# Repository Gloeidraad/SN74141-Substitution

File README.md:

The SN74141 is an obsolete device intended for diving nixie tubes. However, even today, enthusiasts still love nixie tubes. Sometimes by building digital clocks with nixies, but also keeping vintage equivalent alive. In the old days, very often the nixie tubes are driven by the good old SN74141 device. These devices (or the soviet K155ID1) can still be found on the internet, but stocks are dwindling. I tried to make a replacement circuit which should fit on the location of the original DIL-16 footprint of the SN74141. 

Because of the limited size of the DIL-16 socket, I had to use the smallest devices possible, so if you want to use the design, be sure you are capable to solder TSSOP devices.

The design is not implement on a real PCBA yet, so please test it yourself before placing it in al valuable instrument.

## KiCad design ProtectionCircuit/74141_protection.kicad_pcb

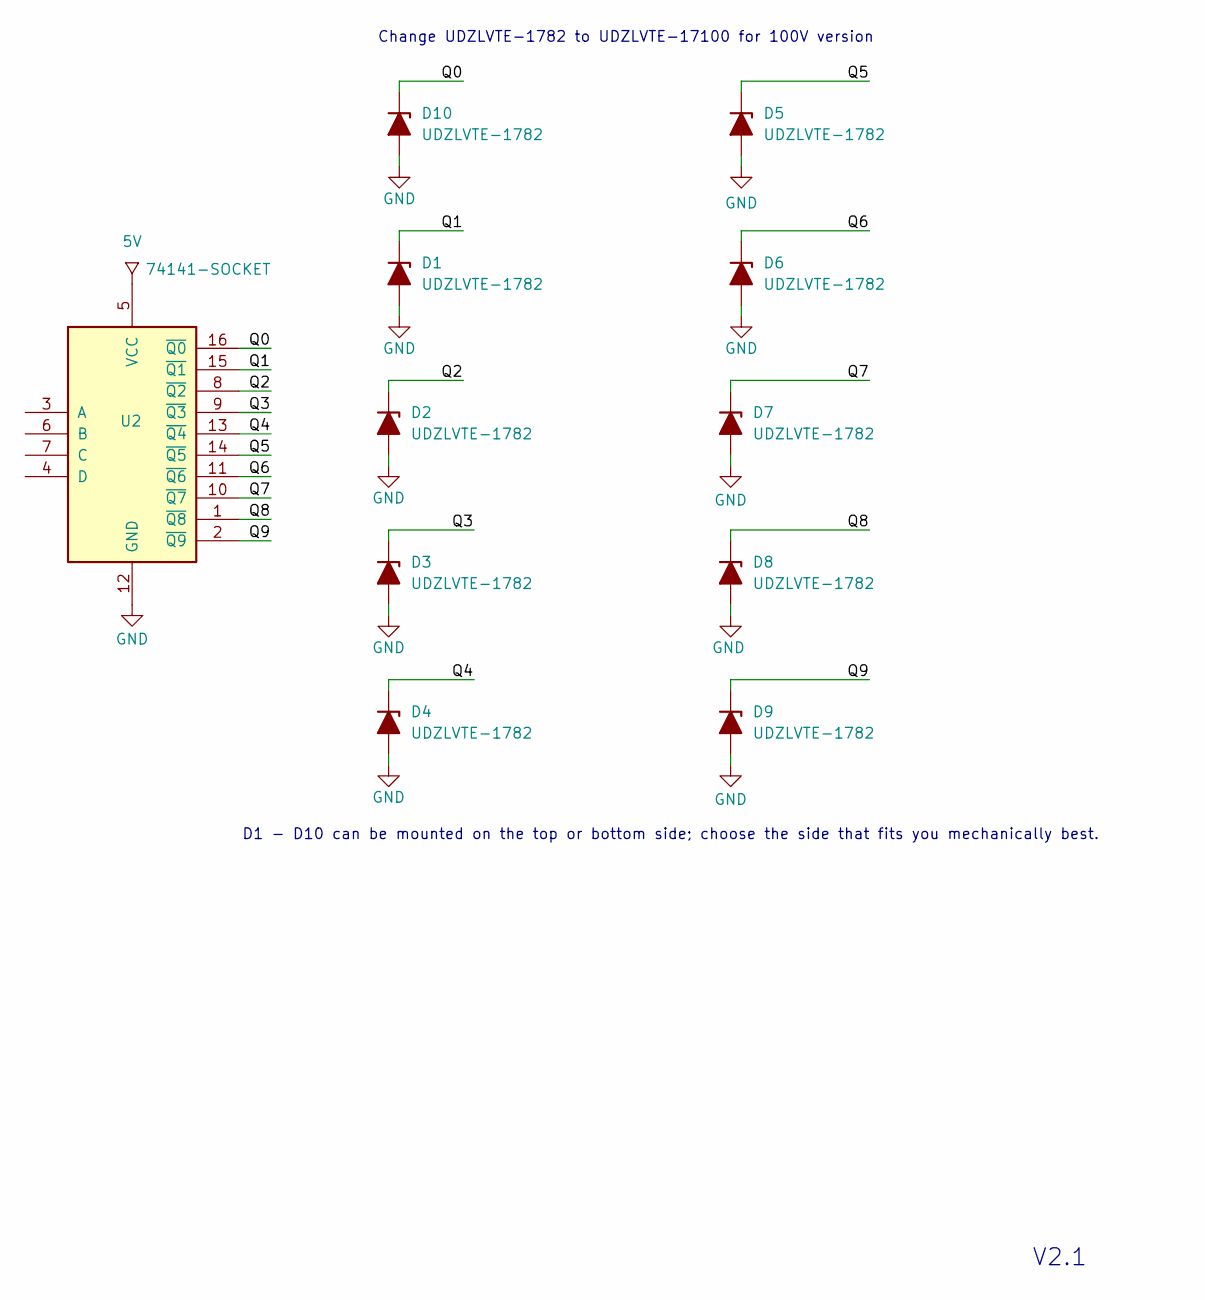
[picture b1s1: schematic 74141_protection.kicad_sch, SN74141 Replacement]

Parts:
D1, D2, D3, D4, D5, D6, D7, D8, D9, D10: UDZLVTE-1782; SOD-323-HandSoldering-dual-side
U2: 74141-SOCKET; DIP-16-header-type2

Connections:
5V: U2.5 (VCC)
/Q0: D10.1 (K), U2.16 (~Q0)
/Q1: D1.1 (K), U2.15 (~Q1)
/Q2: D2.1 (K), U2.8 (~Q2)
/Q3: D3.1 (K), U2.9 (~Q3)
/Q4: D4.1 (K), U2.13 (~Q4)
/Q5: D5.1 (K), U2.14 (~Q5)
/Q6: D6.1 (K), U2.11 (~Q6)
/Q7: D7.1 (K), U2.10 (~Q7)
/Q8: D8.1 (K), U2.1 (~Q8)
/Q9: D9.1 (K), U2.2 (~Q9)
GND: D1.2 (A), D2.2 (A), D3.2 (A), D4.2 (A), D5.2 (A), D6.2 (A), D7.2 (A), D8.2 (A), D9.2 (A), D10.2 (A), U2.12 (GND)

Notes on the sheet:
D1 - D10 can be mounted on the top or bottom side; choose the side that fits you mechanically best.
Change UDZLVTE-1782 to UDZLVTE-17100 for 100V version
V2.1

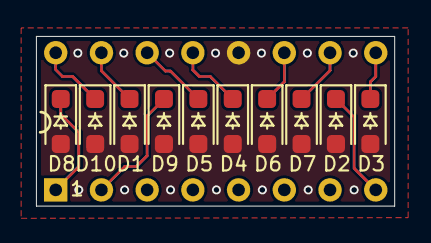
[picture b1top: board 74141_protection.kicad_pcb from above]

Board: 2 copper layers, 19.9 x 9.4 mm, 11 parts (0 on the bottom side), 11 nets.

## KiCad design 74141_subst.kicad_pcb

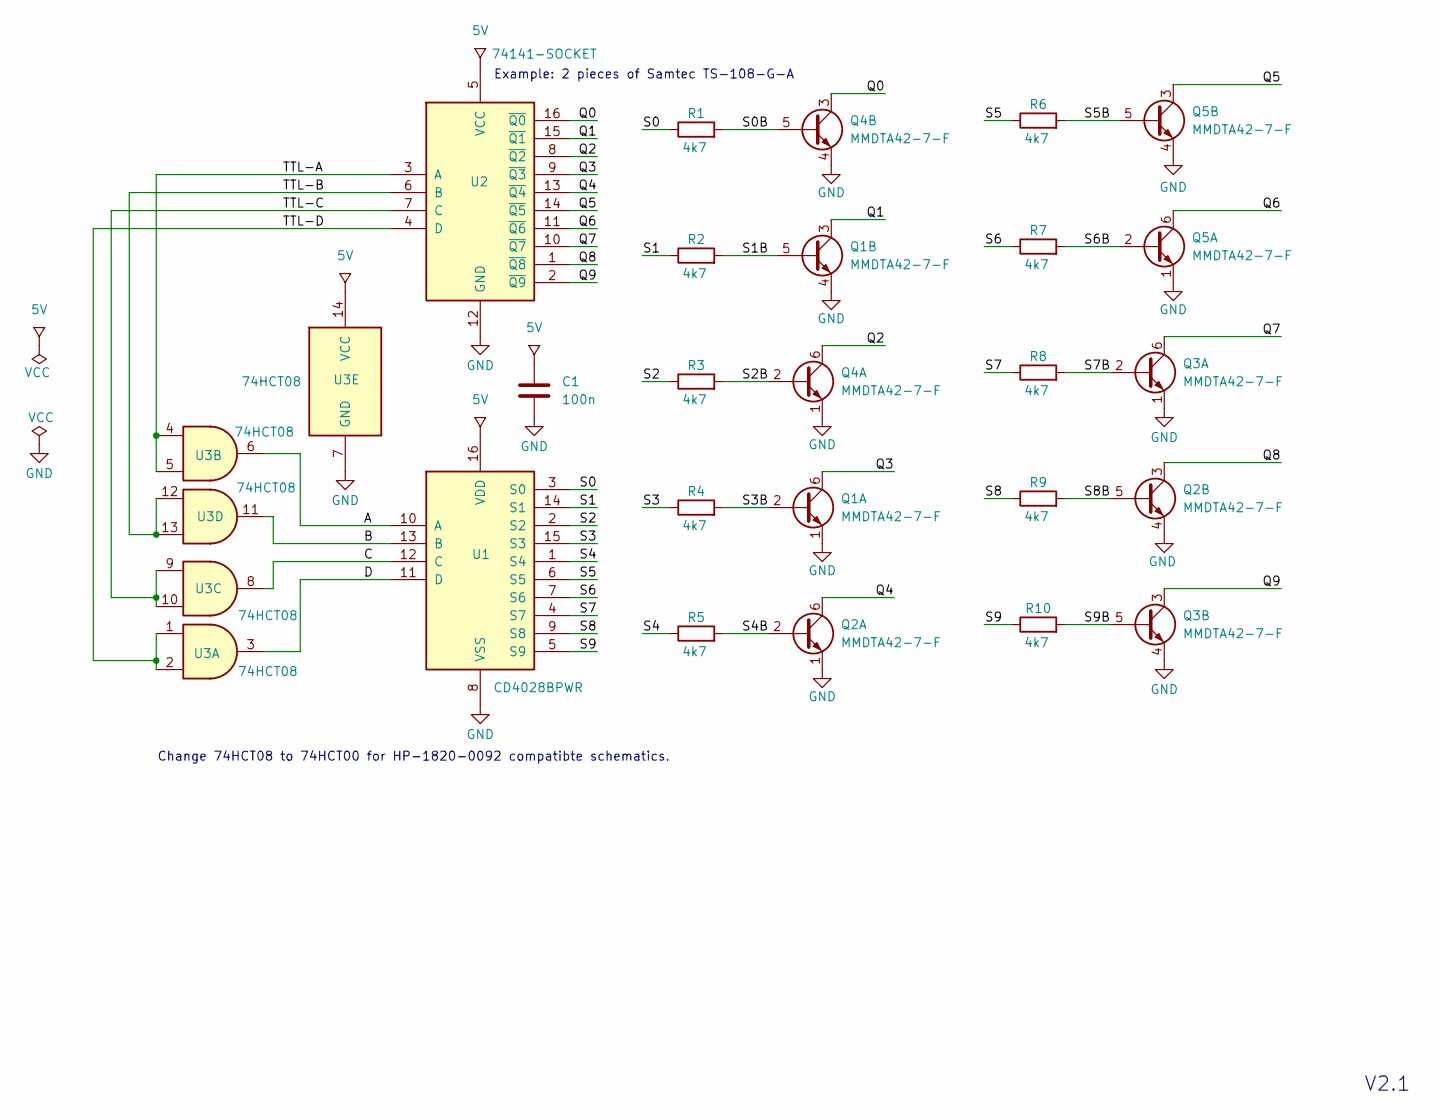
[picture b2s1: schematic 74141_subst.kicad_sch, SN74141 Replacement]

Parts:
C1: 100n; C_0402_1005Metric
Q1, Q3: MMDTA42-7-F; SOT-26
Q2, Q4, Q5: MMDTA42-7-F; SOT-26-V2
R1, R2, R3, R4, R5, R6, R7, R8, R9, R10: 4k7; R_0402_Pad0.72x0.64mm_HandSolder
U1: CD4028BPWR; TSSOP-16_4.4x5mm_P0.65mm
U2: 74141-SOCKET; DIP-16-header-type2
U3: 74HCT08; TSSOP-14_4.4x5mm_P0.65mm

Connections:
5V: C1.1, U1.16 (VDD), U2.5 (VCC), U3.14 (VCC)
/A: U1.10 (A), U3.6
/B: U1.13 (B), U3.11
/C: U1.12 (C), U3.8
/D: U1.11 (D), U3.3
/Q0: Q4.3 (C2), U2.16 (~Q0)
/Q1: Q1.3 (C2), U2.15 (~Q1)
/Q2: Q4.6 (C1), U2.8 (~Q2)
/Q3: Q1.6 (C1), U2.9 (~Q3)
/Q4: Q2.6 (C1), U2.13 (~Q4)
/Q5: Q5.3 (C2), U2.14 (~Q5)
/Q6: Q5.6 (C1), U2.11 (~Q6)
/Q7: Q3.6 (C1), U2.10 (~Q7)
/Q8: Q2.3 (C2), U2.1 (~Q8)
/Q9: Q3.3 (C2), U2.2 (~Q9)
/S0: R1.1, U1.3 (S0)
/S0B: Q4.5 (B2), R1.2
/S1: R2.1, U1.14 (S1)
/S1B: Q1.5 (B2), R2.2
/S2: R3.1, U1.2 (S2)
/S2B: Q4.2 (B1), R3.2
/S3: R4.1, U1.15 (S3)
/S3B: Q1.2 (B1), R4.2
/S4: R5.1, U1.1 (S4)
/S4B: Q2.2 (B1), R5.2
/S5: R6.1, U1.6 (S5)
/S5B: Q5.5 (B2), R6.2
/S6: R7.1, U1.7 (S6)
/S6B: Q5.2 (B1), R7.2
/S7: R8.1, U1.4 (S7)
/S7B: Q3.2 (B1), R8.2
/S8: R9.1, U1.9 (S8)
/S8B: Q2.5 (B2), R9.2
/S9: R10.1, U1.5 (S9)
/S9B: Q3.5 (B2), R10.2
/TTL-A: U2.3 (A), U3.4, U3.5
/TTL-B: U2.6 (B), U3.12, U3.13
/TTL-C: U2.7 (C), U3.9, U3.10
/TTL-D: U2.4 (D), U3.1, U3.2
GND: C1.2, Q1.1 (E1), Q1.4 (E2), Q2.1 (E1), Q2.4 (E2), Q3.1 (E1), Q3.4 (E2), Q4.1 (E1), Q4.4 (E2), Q5.1 (E1), Q5.4 (E2), U1.8 (VSS), U2.12 (GND), U3.7 (GND)

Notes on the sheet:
Example: 2 pieces of Samtec TS-108-G-A
Change 74HCT08 to 74HCT00 for HP-1820-0092 compatibte schematics.
V2.1

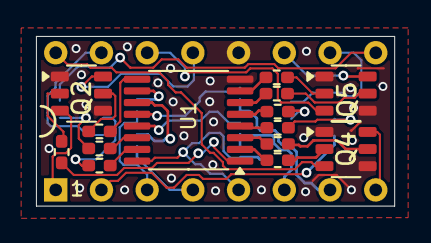
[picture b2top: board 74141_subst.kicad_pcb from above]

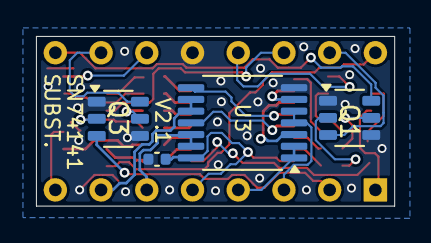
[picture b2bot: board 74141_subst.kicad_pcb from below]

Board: 2 copper layers, 19.9 x 9.4 mm, 19 parts (4 on the bottom side), 40 nets.

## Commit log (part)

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2025-03-30 Removed some typos
2025-04-01 Added info in silk
